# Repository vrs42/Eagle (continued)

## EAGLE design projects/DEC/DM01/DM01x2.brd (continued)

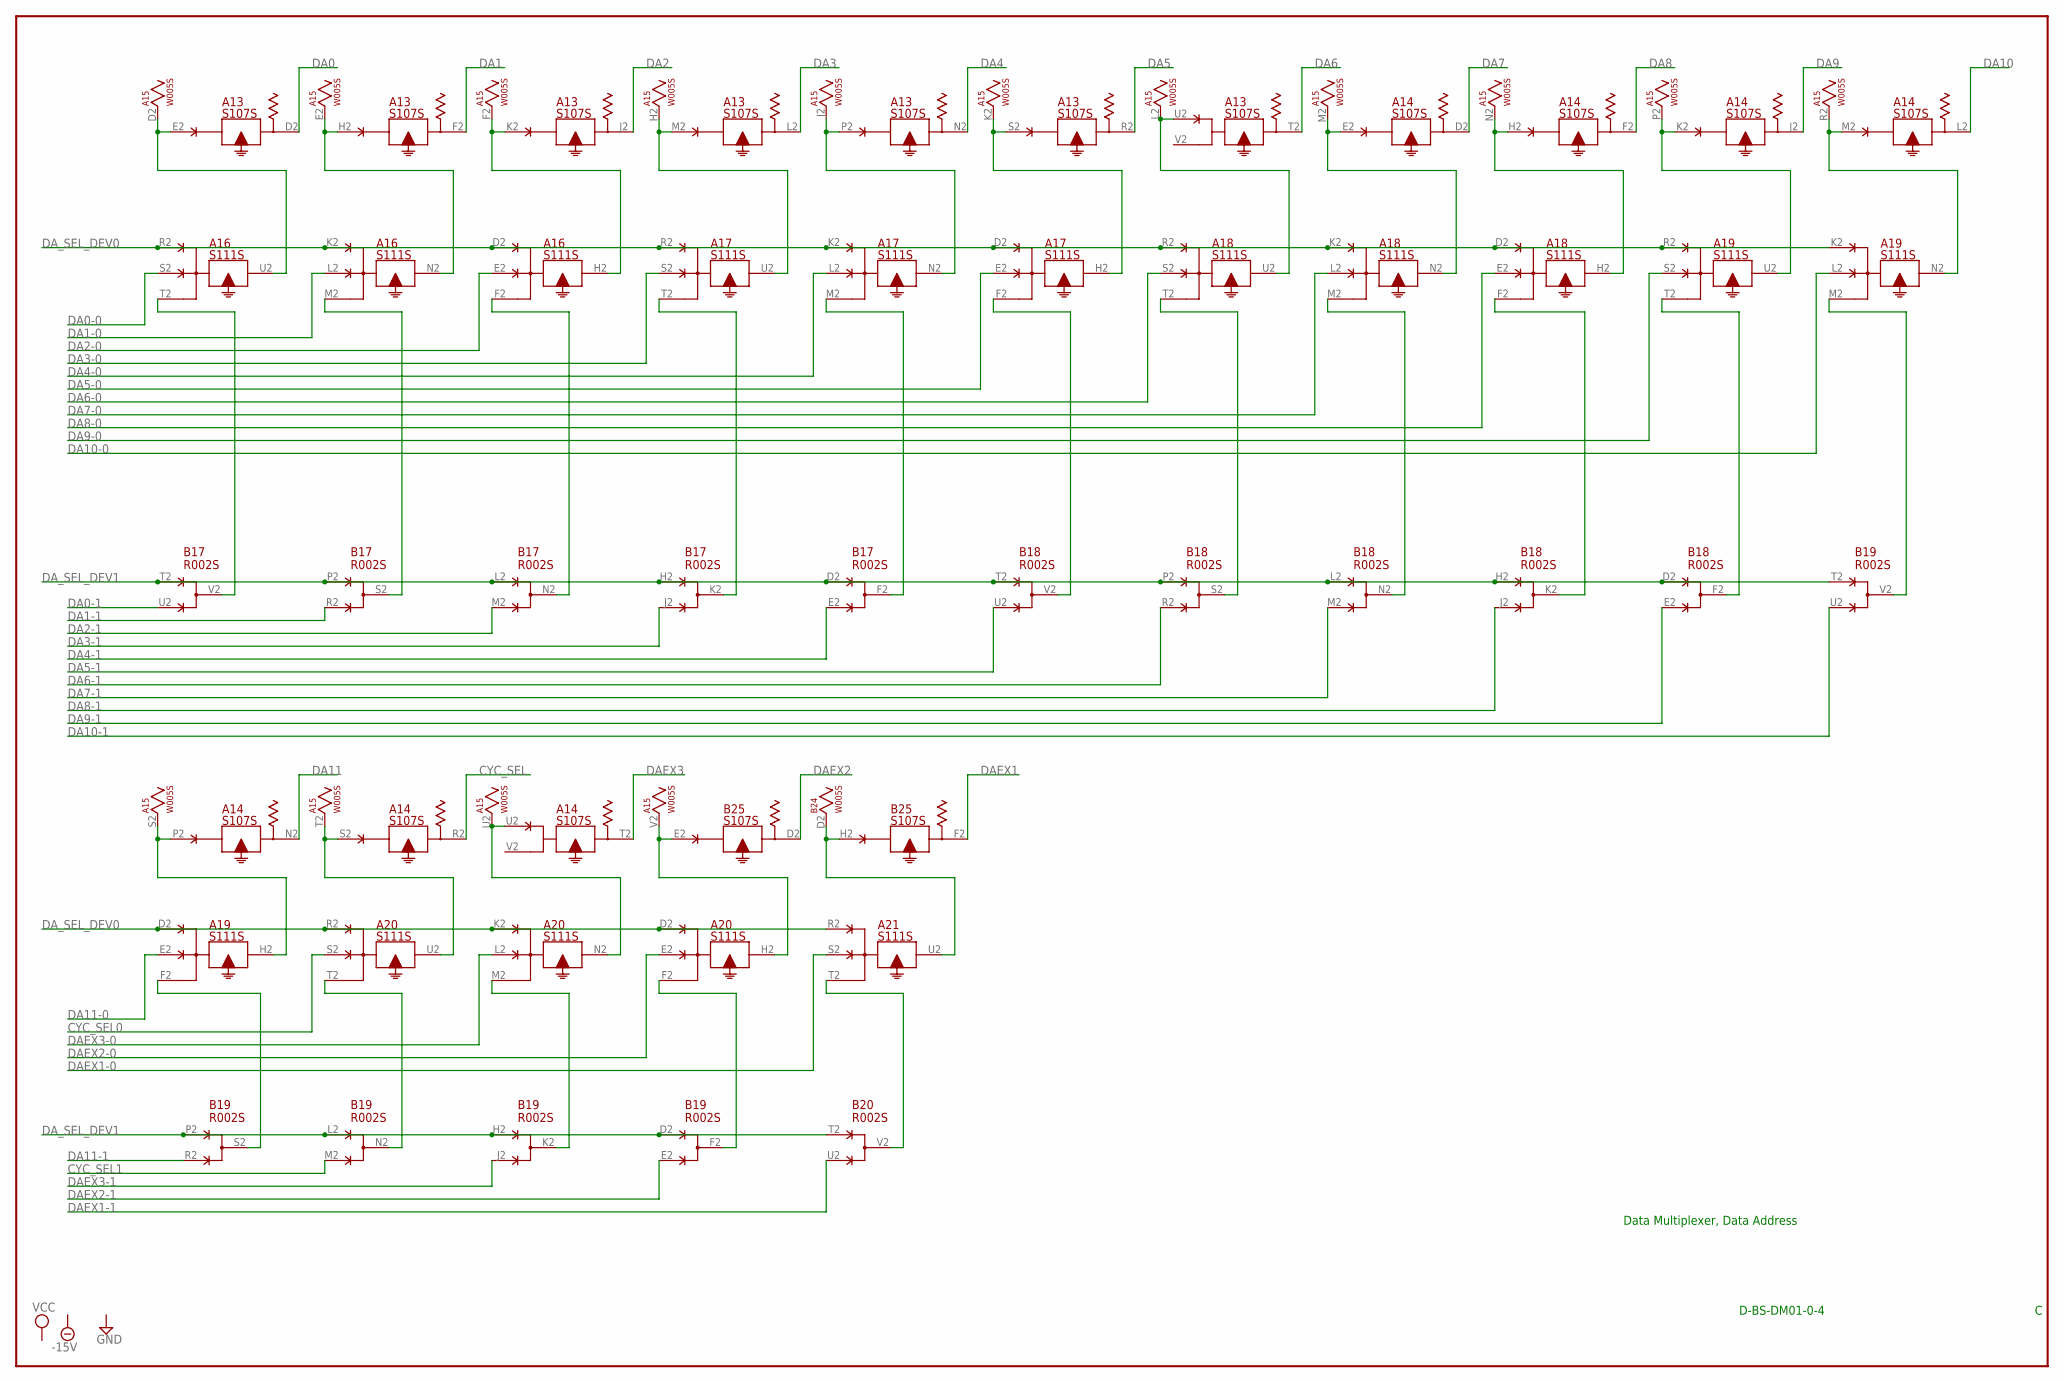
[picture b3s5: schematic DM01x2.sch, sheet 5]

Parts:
A13, A14: S107S; H807S
A15: W005S; H807S
A16, A17, A18, A19, A20, A21: S111S; H807S
B17, B18, B19, B20: R002S; H807S
B24: W005S; H807S
B25: S107S; H807S

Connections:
-15V: A13.B2 (-15V), A14.B2 (-15V), A15.B2 (-15V), A16.B2 (-15V), A17.B2 (-15V), A18.B2 (-15V), A19.B2 (-15V), A20.B2 (-15V), A21.B2 (-15V), B17.B2 (-15V), B18.B2 (-15V), B19.B2 (-15V), B20.B2 (-15V), B24.B2 (-15V), B25.B2 (-15V); also elsewhere on the board
CYC_SEL: A14.R2; also elsewhere on the board
CYC_SEL0: A20.S2; also elsewhere on the board
CYC_SEL1: B19.M2 (E); also elsewhere on the board
DA0: A13.D2; also elsewhere on the board
DA0-0: A16.S2; also elsewhere on the board
DA0-1: B17.U2 (E); also elsewhere on the board
DA1: A13.F2; also elsewhere on the board
DA1-0: A16.L2; also elsewhere on the board
DA1-1: B17.R2 (E); also elsewhere on the board
DA2: A13.J2; also elsewhere on the board
DA2-0: A16.E2; also elsewhere on the board
DA2-1: B17.M2 (E); also elsewhere on the board
DA3: A13.L2; also elsewhere on the board
DA3-0: A17.S2; also elsewhere on the board
DA3-1: B17.J2 (E); also elsewhere on the board
DA4: A13.N2; also elsewhere on the board
DA4-0: A17.L2; also elsewhere on the board
DA4-1: B17.E2 (E); also elsewhere on the board
DA5: A13.R2; also elsewhere on the board
DA5-0: A17.E2; also elsewhere on the board
DA5-1: B18.U2 (E); also elsewhere on the board
DA6: A13.T2; also elsewhere on the board
DA6-0: A18.S2; also elsewhere on the board
DA6-1: B18.R2 (E); also elsewhere on the board
DA7: A14.D2; also elsewhere on the board
DA7-0: A18.L2; also elsewhere on the board
DA7-1: B18.M2 (E); also elsewhere on the board
DA8: A14.F2; also elsewhere on the board
DA8-0: A18.E2; also elsewhere on the board
DA8-1: B18.J2 (E); also elsewhere on the board
DA9: A14.J2; also elsewhere on the board
DA9-0: A19.S2; also elsewhere on the board
DA9-1: B18.E2 (E); also elsewhere on the board
DA10: A14.L2; also elsewhere on the board
DA10-0: A19.L2; also elsewhere on the board
DA10-1: B19.U2 (E); also elsewhere on the board
DA11: A14.N2; also elsewhere on the board
DA11-0: A19.E2; also elsewhere on the board
DA11-1: B19.R2 (E); also elsewhere on the board
DAEX1: B25.F2; also elsewhere on the board
DAEX1-0: A21.S2; also elsewhere on the board
DAEX1-1: B20.U2 (E); also elsewhere on the board
DAEX2: B25.D2; also elsewhere on the board
DAEX2-0: A20.E2; also elsewhere on the board
DAEX2-1: B19.E2 (E); also elsewhere on the board
DAEX3: A14.T2; also elsewhere on the board
DAEX3-0: A20.L2; also elsewhere on the board
DAEX3-1: B19.J2 (E); also elsewhere on the board
DA_SEL_DEV0: A16.D2, A16.K2, A16.R2, A17.D2, A17.K2, A17.R2, A18.D2, A18.K2, A18.R2, A19.D2, A19.K2, A19.R2, A20.D2, A20.K2, A20.R2, A21.R2; also elsewhere on the board
DA_SEL_DEV1: B17.D2 (D), B17.H2 (D), B17.L2 (D), B17.P2 (D), B17.T2 (D), B18.D2 (D), B18.H2 (D), B18.L2 (D), B18.P2 (D), B18.T2 (D), B19.D2 (D), B19.H2 (D), B19.L2 (D), B19.P2 (D), B19.T2 (D), B20.T2 (D); also elsewhere on the board
GND: A13.C2 (GND), A14.C2 (GND), A15.C2 (GND), A16.C2 (GND), A17.C2 (GND), A18.C2 (GND), A19.C2 (GND), A20.C2 (GND), A21.C2 (GND), B17.C2 (GND), B18.C2 (GND), B19.C2 (GND), B20.C2 (GND), B24.C2 (GND), B25.C2 (GND); also elsewhere on the board
unnamed: A19.F2, B19.S2 (F)
unnamed: A20.T2, B19.N2 (F)
unnamed: A20.M2, B19.K2 (F)
unnamed: A20.F2, B19.F2 (F)
unnamed: A21.T2, B20.V2 (F)
unnamed: A16.T2, B17.V2 (F)
unnamed: A19.M2, B19.V2 (F)
unnamed: A19.T2, B18.F2 (F)
unnamed: A18.F2, B18.K2 (F)
unnamed: A18.M2, B18.N2 (F)
unnamed: A18.T2, B18.S2 (F)
unnamed: A17.F2, B18.V2 (F)
unnamed: A17.M2, B17.F2 (F)
unnamed: A17.T2, B17.K2 (F)
unnamed: A16.F2, B17.N2 (F)
unnamed: A16.M2, B17.S2 (F)
unnamed: A13.E2, A15.D2, A16.U2
unnamed: A13.U2, A15.L2, A18.U2
unnamed: A13.H2, A15.E2, A16.N2
unnamed: A13.K2, A15.F2, A16.H2
unnamed: A13.M2, A15.H2, A17.U2
unnamed: A13.P2, A15.J2, A17.N2
unnamed: A13.S2, A15.K2, A17.H2
unnamed: A14.E2, A15.M2, A18.N2
unnamed: A14.H2, A15.N2, A18.H2
unnamed: A14.K2, A15.P2, A19.U2
unnamed: A14.M2, A15.R2, A19.N2
unnamed: A14.P2, A15.S2, A19.H2
unnamed: A14.S2, A15.T2, A20.U2
unnamed: A14.U2, A15.U2, A20.N2
unnamed: A15.V2, A20.H2, B25.E2
unnamed: A21.U2, B24.D2, B25.H2
VCC: A13.A2 (VCC), A14.A2 (VCC), A15.A2 (VCC), A16.A2 (VCC), A17.A2 (VCC), A18.A2 (VCC), A19.A2 (VCC), A20.A2 (VCC), A21.A2 (VCC), B17.A2 (VCC), B18.A2 (VCC), B19.A2 (VCC), B20.A2 (VCC), B24.A2 (VCC), B25.A2 (VCC); also elsewhere on the board

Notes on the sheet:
D-BS-DM01-0-4
Data Multiplexer, Data Address

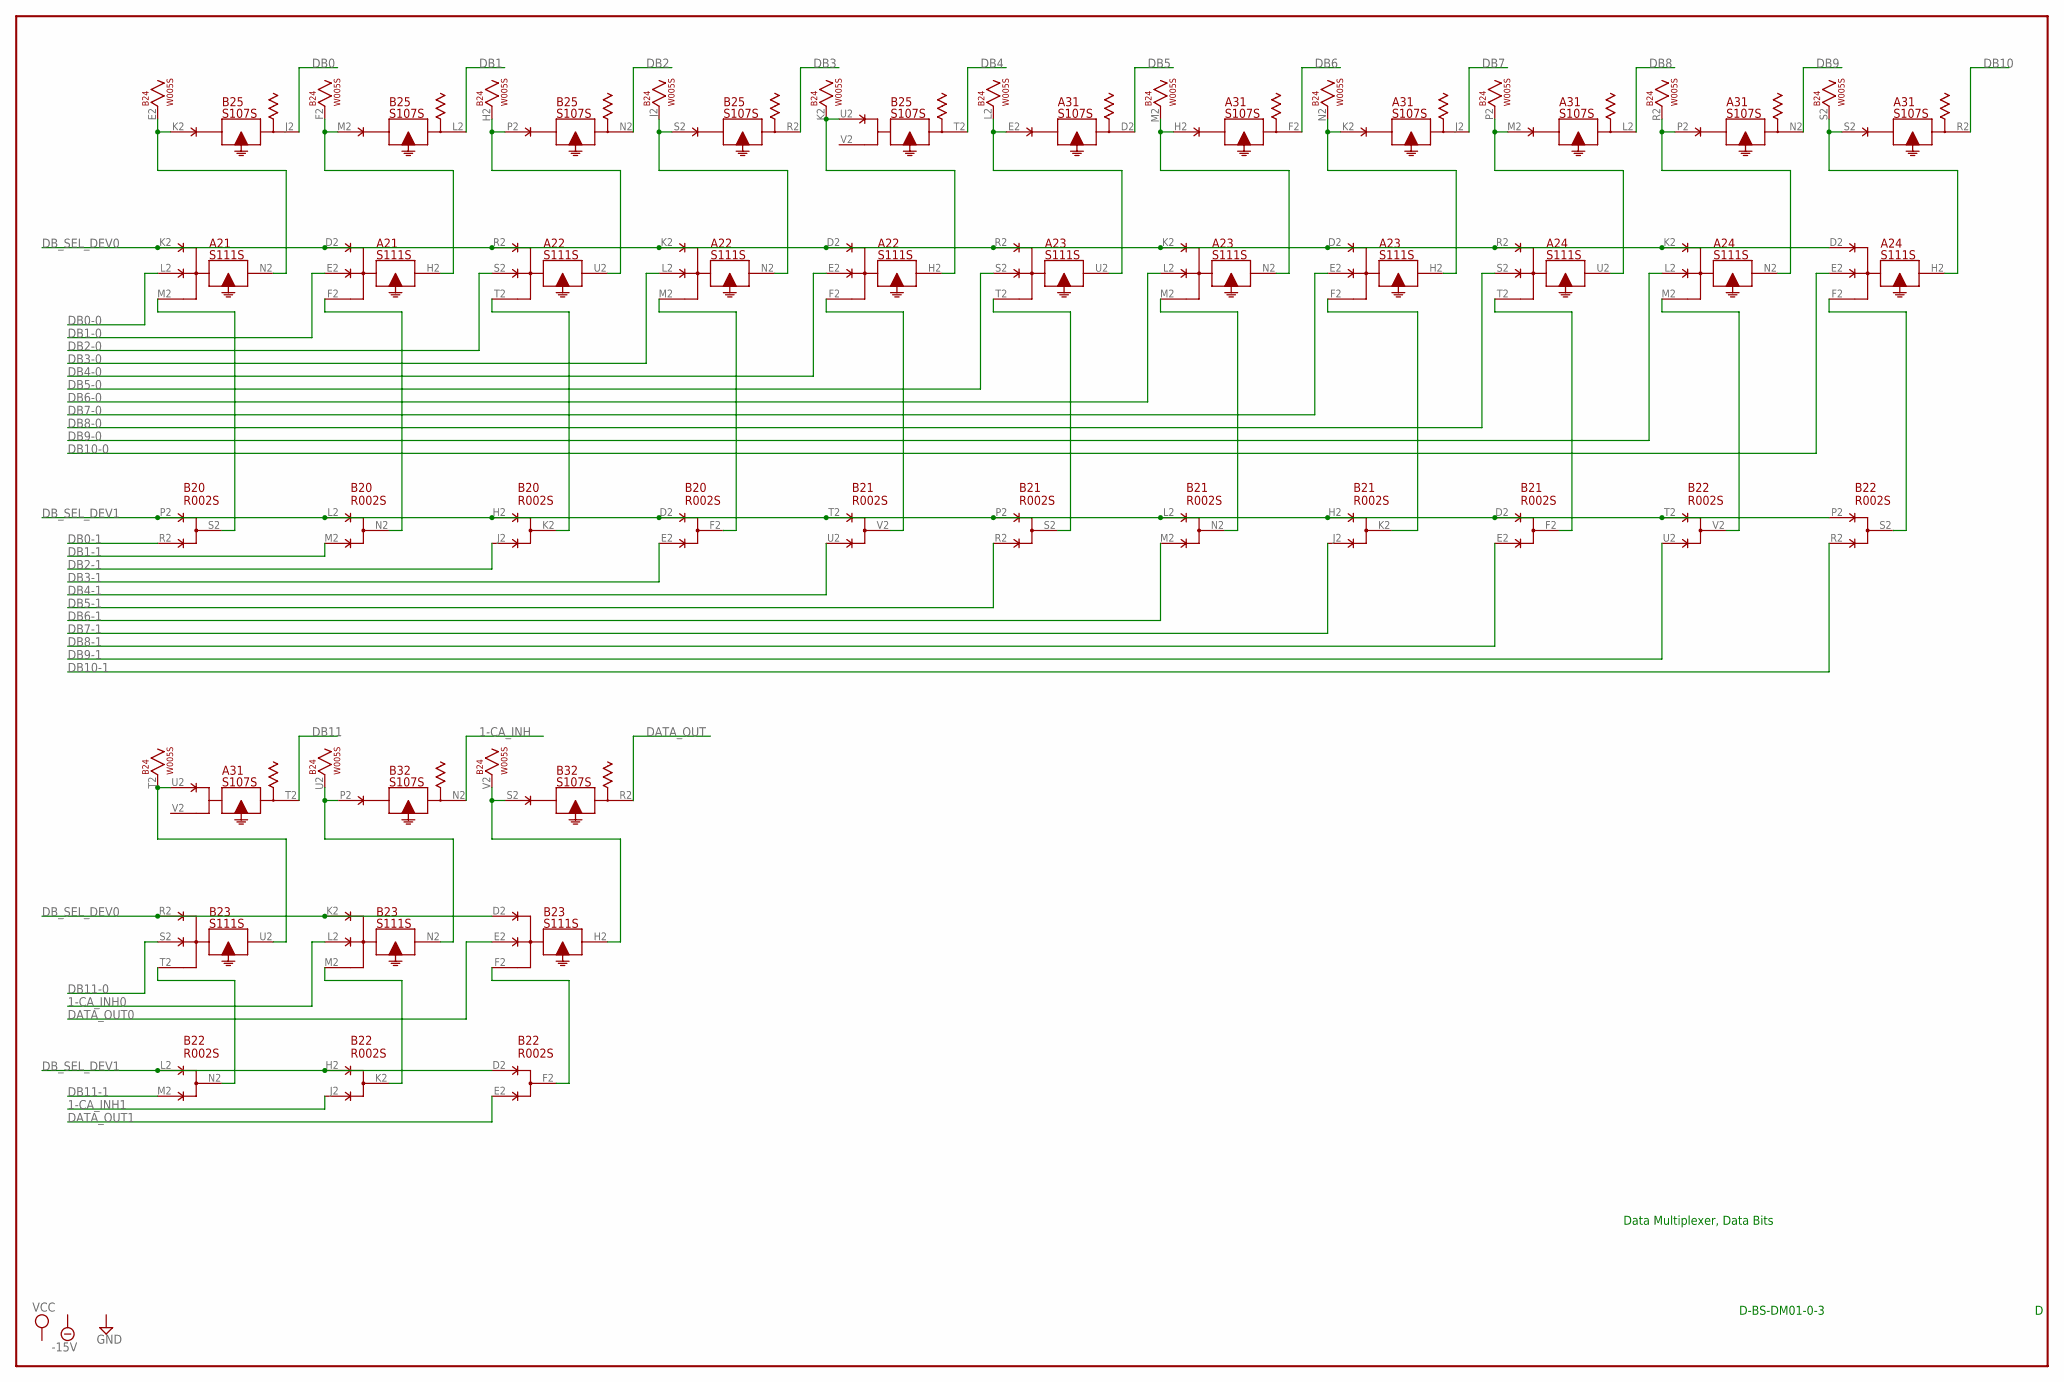
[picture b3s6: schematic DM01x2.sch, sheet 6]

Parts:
A21, A22, A23, A24: S111S; H807S
A31: S107S; H807S
B20, B21, B22: R002S; H807S
B23: S111S; H807S
B24: W005S; H807S
B25, B32: S107S; H807S

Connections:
1-CA_INH: B32.N2; also elsewhere on the board
1-CA_INH0: B23.L2; also elsewhere on the board
1-CA_INH1: B22.J2 (E); also elsewhere on the board
-15V: A21.B2 (-15V), A22.B2 (-15V), A23.B2 (-15V), A24.B2 (-15V), A31.B2 (-15V), B20.B2 (-15V), B21.B2 (-15V), B22.B2 (-15V), B23.B2 (-15V), B24.B2 (-15V), B25.B2 (-15V), B32.B2 (-15V); also elsewhere on the board
DATA_OUT: B32.R2; also elsewhere on the board
DATA_OUT0: B23.E2; also elsewhere on the board
DATA_OUT1: B22.E2 (E); also elsewhere on the board
DB0: B25.J2; also elsewhere on the board
DB0-0: A21.L2; also elsewhere on the board
DB0-1: B20.R2 (E); also elsewhere on the board
DB1: B25.L2; also elsewhere on the board
DB1-0: A21.E2; also elsewhere on the board
DB1-1: B20.M2 (E); also elsewhere on the board
DB2: B25.N2; also elsewhere on the board
DB2-0: A22.S2; also elsewhere on the board
DB2-1: B20.J2 (E); also elsewhere on the board
DB3: B25.R2; also elsewhere on the board
DB3-0: A22.L2; also elsewhere on the board
DB3-1: B20.E2 (E); also elsewhere on the board
DB4: B25.T2; also elsewhere on the board
DB4-0: A22.E2; also elsewhere on the board
DB4-1: B21.U2 (E); also elsewhere on the board
DB5: A31.D2; also elsewhere on the board
DB5-0: A23.S2; also elsewhere on the board
DB5-1: B21.R2 (E); also elsewhere on the board
DB6: A31.F2; also elsewhere on the board
DB6-0: A23.L2; also elsewhere on the board
DB6-1: B21.M2 (E); also elsewhere on the board
DB7: A31.J2; also elsewhere on the board
DB7-0: A23.E2; also elsewhere on the board
DB7-1: B21.J2 (E); also elsewhere on the board
DB8: A31.L2; also elsewhere on the board
DB8-0: A24.S2; also elsewhere on the board
DB8-1: B21.E2 (E); also elsewhere on the board
DB9: A31.N2; also elsewhere on the board
DB9-0: A24.L2; also elsewhere on the board
DB9-1: B22.U2 (E); also elsewhere on the board
DB10: A31.R2; also elsewhere on the board
DB10-0: A24.E2; also elsewhere on the board
DB10-1: B22.R2 (E); also elsewhere on the board
DB11: A31.T2; also elsewhere on the board
DB11-0: B23.S2; also elsewhere on the board
DB11-1: B22.M2 (E); also elsewhere on the board
DB_SEL_DEV0: A21.D2, A21.K2, A22.D2, A22.K2, A22.R2, A23.D2, A23.K2, A23.R2, A24.D2, A24.K2, A24.R2, B23.D2, B23.K2, B23.R2; also elsewhere on the board
DB_SEL_DEV1: B20.D2 (D), B20.H2 (D), B20.L2 (D), B20.P2 (D), B21.D2 (D), B21.H2 (D), B21.L2 (D), B21.P2 (D), B21.T2 (D), B22.D2 (D), B22.H2 (D), B22.L2 (D), B22.P2 (D), B22.T2 (D); also elsewhere on the board
GND: A21.C2 (GND), A22.C2 (GND), A23.C2 (GND), A24.C2 (GND), A31.C2 (GND), B20.C2 (GND), B21.C2 (GND), B22.C2 (GND), B23.C2 (GND), B24.C2 (GND), B25.C2 (GND), B32.C2 (GND); also elsewhere on the board
unnamed: B22.F2 (F), B23.F2
unnamed: B22.N2 (F), B23.T2
unnamed: B22.K2 (F), B23.M2
unnamed: A24.F2, B22.S2 (F)
unnamed: A21.M2, B20.S2 (F)
unnamed: A21.F2, B20.N2 (F)
unnamed: A22.T2, B20.K2 (F)
unnamed: A22.M2, B20.F2 (F)
unnamed: A22.F2, B21.V2 (F)
unnamed: A23.T2, B21.S2 (F)
unnamed: A23.M2, B21.N2 (F)
unnamed: A23.F2, B21.K2 (F)
unnamed: A24.T2, B21.F2 (F)
unnamed: A24.M2, B22.V2 (F)
unnamed: A21.N2, B24.E2, B25.K2
unnamed: A21.H2, B24.F2, B25.M2
unnamed: A22.U2, B24.H2, B25.P2
unnamed: A22.N2, B24.J2, B25.S2
unnamed: A22.H2, B24.K2, B25.U2
unnamed: A23.U2, A31.E2, B24.L2
unnamed: A23.N2, A31.H2, B24.M2
unnamed: A23.H2, A31.K2, B24.N2
unnamed: A24.U2, A31.M2, B24.P2
unnamed: A24.N2, A31.P2, B24.R2
unnamed: A24.H2, A31.S2, B24.S2
unnamed: A31.U2, B23.U2, B24.T2
unnamed: B23.N2, B24.U2, B32.P2
unnamed: B23.H2, B24.V2, B32.S2
VCC: A21.A2 (VCC), A22.A2 (VCC), A23.A2 (VCC), A24.A2 (VCC), A31.A2 (VCC), B20.A2 (VCC), B21.A2 (VCC), B22.A2 (VCC), B23.A2 (VCC), B24.A2 (VCC), B25.A2 (VCC), B32.A2 (VCC); also elsewhere on the board

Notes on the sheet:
D-BS-DM01-0-3
Data Multiplexer, Data Bits

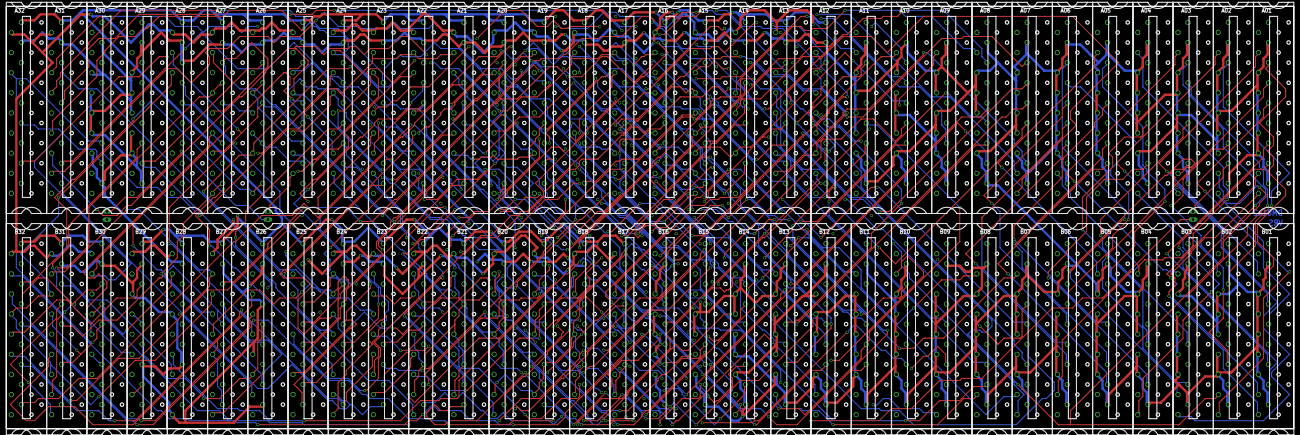
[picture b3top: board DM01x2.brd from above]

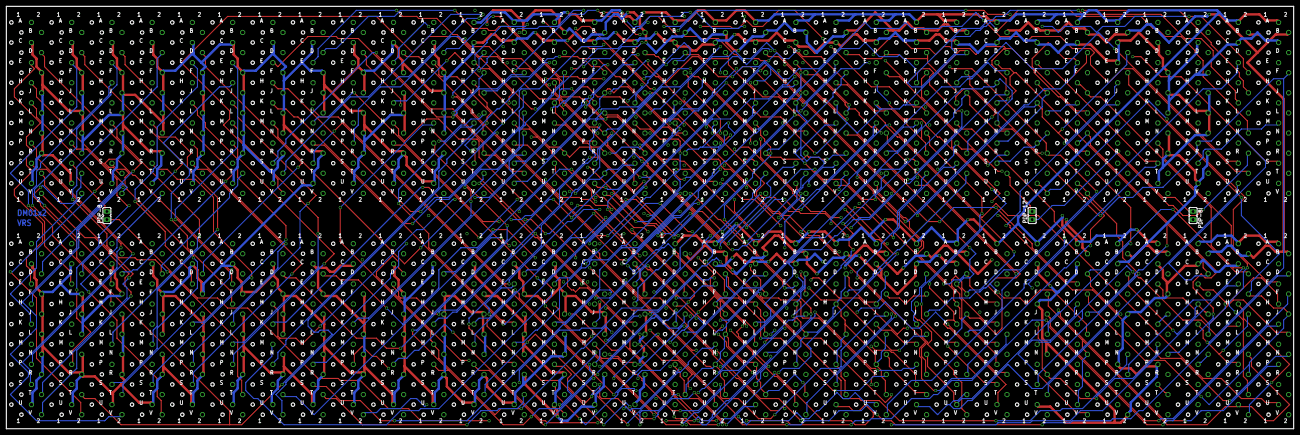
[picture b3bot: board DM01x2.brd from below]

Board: 4 copper layers, 406.4 x 133.3 mm, 75 parts (3 on the bottom side), 256 nets.

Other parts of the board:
U$9, U$10, U$11, U$12, U$13, U$14, U$15, U$16: CBLOCK

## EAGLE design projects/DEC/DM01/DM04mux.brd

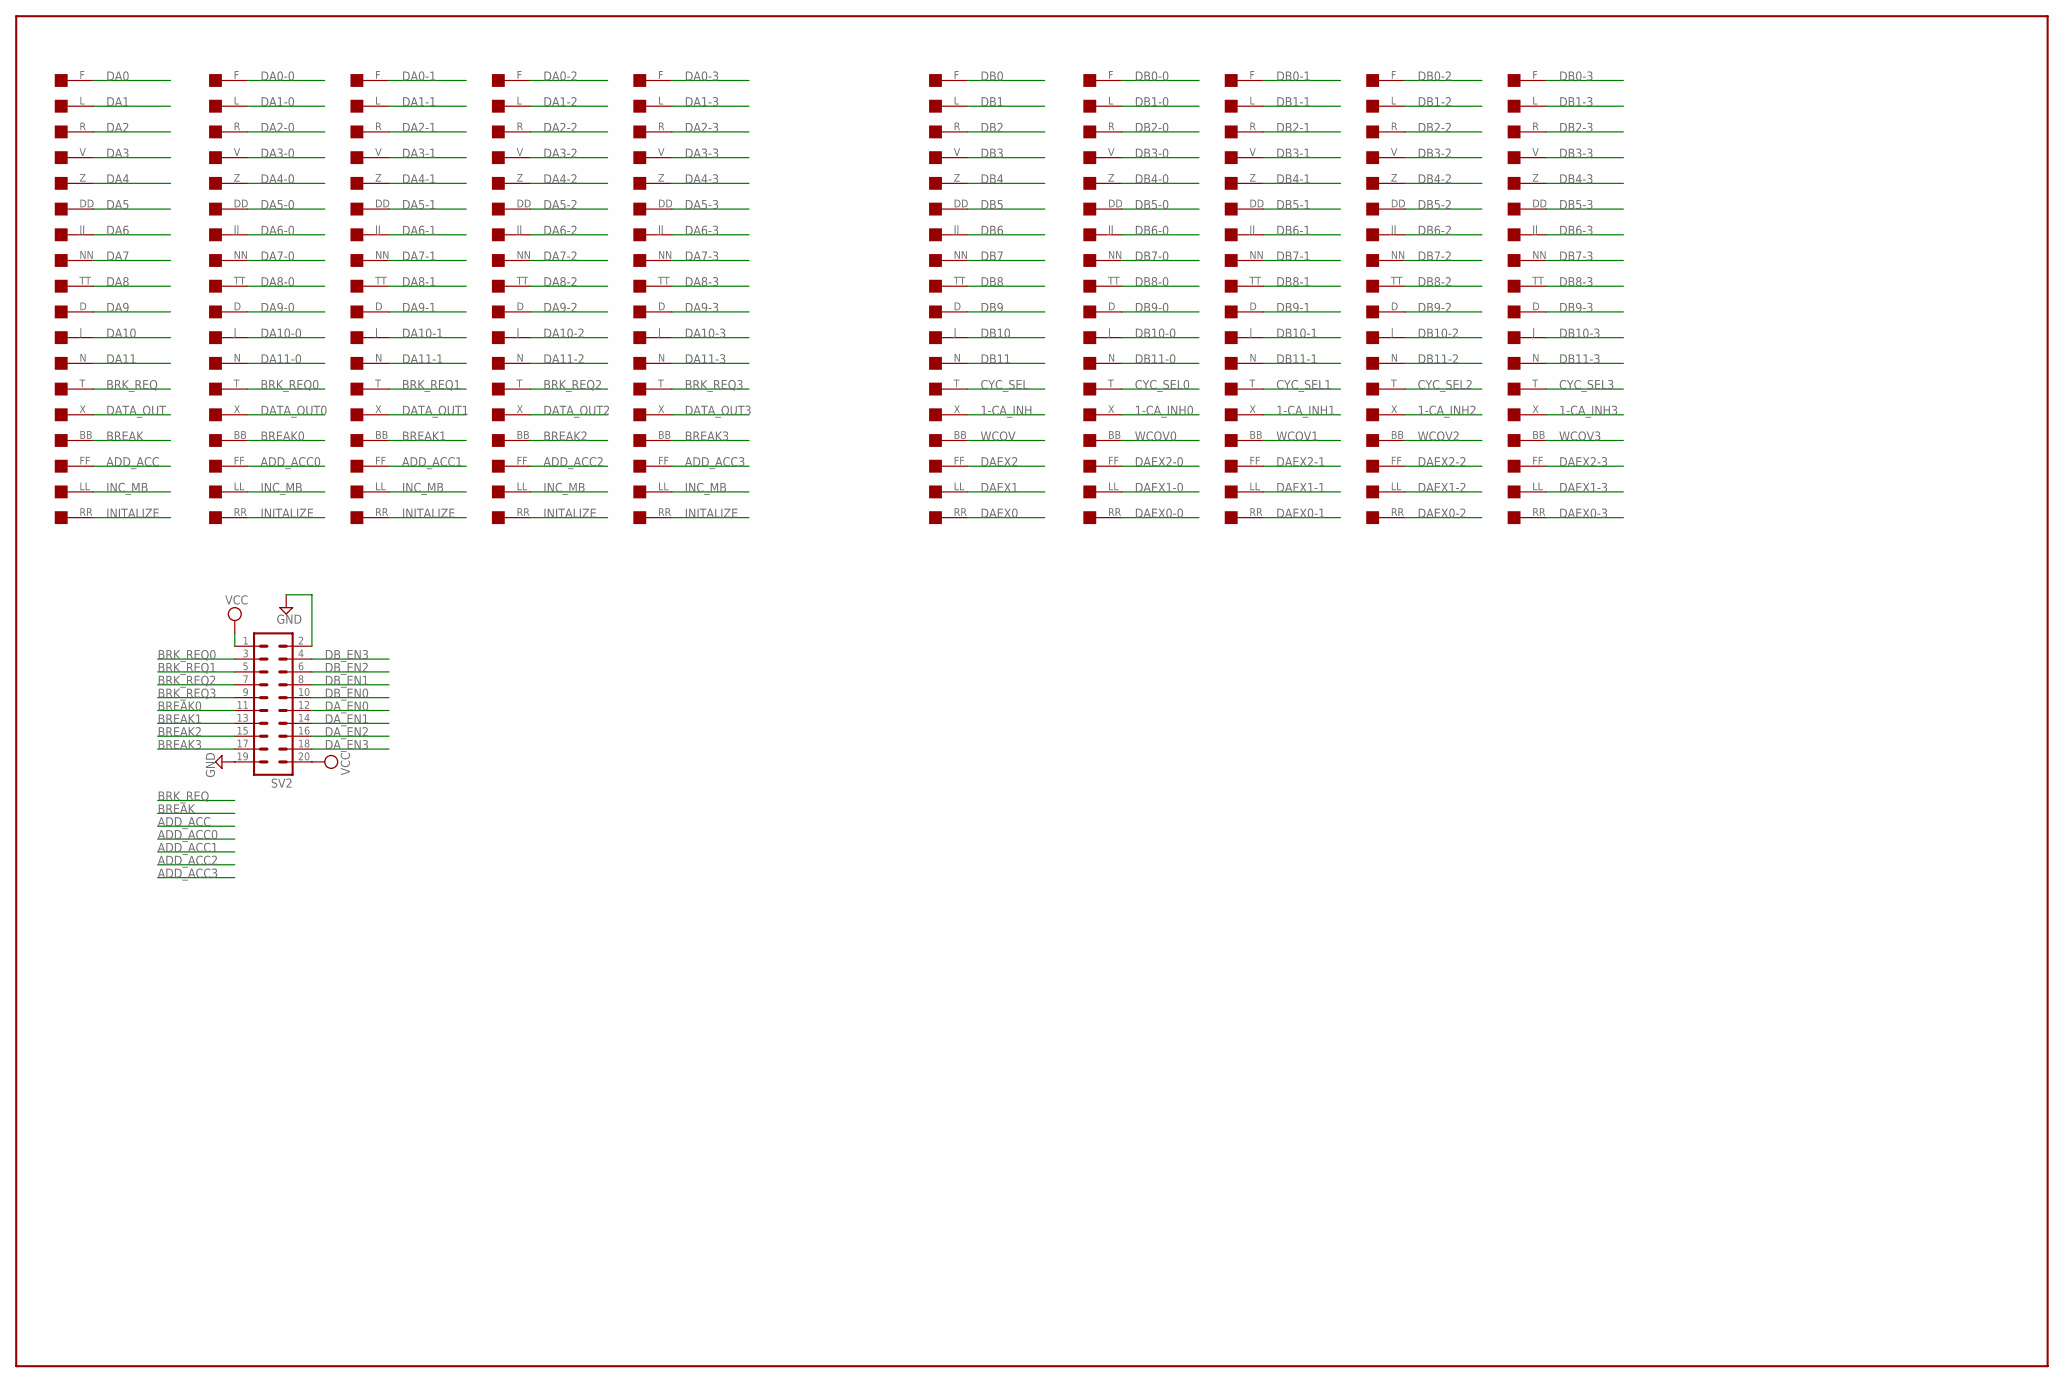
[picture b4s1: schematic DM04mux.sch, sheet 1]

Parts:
SV2: MA10-2
U$1, U$2, U$3, U$4, U$5, U$6, U$7, U$8, U$9, U$10: BC08J; DEC40PINV

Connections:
1-CA_INH: U$6.X (1); also elsewhere on the board
1-CA_INH0: U$7.X (1); also elsewhere on the board
1-CA_INH1: U$8.X (1); also elsewhere on the board
1-CA_INH2: U$9.X (1); also elsewhere on the board
1-CA_INH3: U$10.X (1); also elsewhere on the board
ADD_ACC: U$1.FF (1)
ADD_ACC0: U$2.FF (1)
ADD_ACC1: U$3.FF (1)
ADD_ACC2: U$4.FF (1)
ADD_ACC3: U$5.FF (1)
BREAK: U$1.BB (1)
BREAK0: SV2.11, U$2.BB (1)
BREAK1: SV2.13, U$3.BB (1)
BREAK2: SV2.15, U$4.BB (1)
BREAK3: SV2.17, U$5.BB (1)
BRK_REQ: U$1.T (1)
BRK_REQ0: SV2.3, U$2.T (1)
BRK_REQ1: SV2.5, U$3.T (1)
BRK_REQ2: SV2.7, U$4.T (1)
BRK_REQ3: SV2.9, U$5.T (1)
CYC_SEL: U$6.T (1); also elsewhere on the board
CYC_SEL0: U$7.T (1); also elsewhere on the board
CYC_SEL1: U$8.T (1); also elsewhere on the board
CYC_SEL2: U$9.T (1); also elsewhere on the board
CYC_SEL3: U$10.T (1); also elsewhere on the board
DA0: U$1.F (1); also elsewhere on the board
DA0-0: U$2.F (1); also elsewhere on the board
DA0-1: U$3.F (1); also elsewhere on the board
DA0-2: U$4.F (1); also elsewhere on the board
DA0-3: U$5.F (1); also elsewhere on the board
DA1: U$1.L (1); also elsewhere on the board
DA1-0: U$2.L (1); also elsewhere on the board
DA1-1: U$3.L (1); also elsewhere on the board
DA1-2: U$4.L (1); also elsewhere on the board
DA1-3: U$5.L (1); also elsewhere on the board
DA2: U$1.R (1); also elsewhere on the board
DA2-0: U$2.R (1); also elsewhere on the board
DA2-1: U$3.R (1); also elsewhere on the board
DA2-2: U$4.R (1); also elsewhere on the board
DA2-3: U$5.R (1); also elsewhere on the board
DA3: U$1.V (1); also elsewhere on the board
DA3-0: U$2.V (1); also elsewhere on the board
DA3-1: U$3.V (1); also elsewhere on the board
DA3-2: U$4.V (1); also elsewhere on the board
DA3-3: U$5.V (1); also elsewhere on the board
DA4: U$1.Z (1); also elsewhere on the board
DA4-0: U$2.Z (1); also elsewhere on the board
DA4-1: U$3.Z (1); also elsewhere on the board
DA4-2: U$4.Z (1); also elsewhere on the board
DA4-3: U$5.Z (1); also elsewhere on the board
DA5: U$1.DD (1); also elsewhere on the board
DA5-0: U$2.DD (1); also elsewhere on the board
DA5-1: U$3.DD (1); also elsewhere on the board
DA5-2: U$4.DD (1); also elsewhere on the board
DA5-3: U$5.DD (1); also elsewhere on the board
DA6: U$1.JJ (1); also elsewhere on the board
DA6-0: U$2.JJ (1); also elsewhere on the board
DA6-1: U$3.JJ (1); also elsewhere on the board
DA6-2: U$4.JJ (1); also elsewhere on the board
DA6-3: U$5.JJ (1); also elsewhere on the board
DA7: U$1.NN (1); also elsewhere on the board
DA7-0: U$2.NN (1); also elsewhere on the board
DA7-1: U$3.NN (1); also elsewhere on the board
DA7-2: U$4.NN (1); also elsewhere on the board
DA7-3: U$5.NN (1); also elsewhere on the board
DA8: U$1.TT (1); also elsewhere on the board
DA8-0: U$2.TT (1); also elsewhere on the board
DA8-1: U$3.TT (1); also elsewhere on the board
DA8-2: U$4.TT (1); also elsewhere on the board
DA8-3: U$5.TT (1); also elsewhere on the board
DA9: U$1.D (1); also elsewhere on the board
DA9-0: U$2.D (1); also elsewhere on the board
DA9-1: U$3.D (1); also elsewhere on the board
DA9-2: U$4.D (1); also elsewhere on the board
DA9-3: U$5.D (1); also elsewhere on the board
DA10: U$1.J (1); also elsewhere on the board
DA10-0: U$2.J (1); also elsewhere on the board
DA10-1: U$3.J (1); also elsewhere on the board
DA10-2: U$4.J (1); also elsewhere on the board
DA10-3: U$5.J (1); also elsewhere on the board
DA11: U$1.N (1); also elsewhere on the board
DA11-0: U$2.N (1); also elsewhere on the board
DA11-1: U$3.N (1); also elsewhere on the board
DA11-2: U$4.N (1); also elsewhere on the board
DA11-3: U$5.N (1); also elsewhere on the board
DAEX0: U$6.RR (1); also elsewhere on the board
DAEX0-0: U$7.RR (1); also elsewhere on the board
DAEX0-1: U$8.RR (1); also elsewhere on the board
DAEX0-2: U$9.RR (1); also elsewhere on the board
DAEX0-3: U$10.RR (1); also elsewhere on the board
DAEX1: U$6.LL (1); also elsewhere on the board
DAEX1-0: U$7.LL (1); also elsewhere on the board
DAEX1-1: U$8.LL (1); also elsewhere on the board
DAEX1-2: U$9.LL (1); also elsewhere on the board
DAEX1-3: U$10.LL (1); also elsewhere on the board
DAEX2: U$6.FF (1); also elsewhere on the board
DAEX2-0: U$7.FF (1); also elsewhere on the board
DAEX2-1: U$8.FF (1); also elsewhere on the board
DAEX2-2: U$9.FF (1); also elsewhere on the board
DAEX2-3: U$10.FF (1); also elsewhere on the board
DATA_OUT: U$1.X (1); also elsewhere on the board
DATA_OUT0: U$2.X (1); also elsewhere on the board
DATA_OUT1: U$3.X (1); also elsewhere on the board
DATA_OUT2: U$4.X (1); also elsewhere on the board
DATA_OUT3: U$5.X (1); also elsewhere on the board
DA_EN0: SV2.12; also elsewhere on the board
DA_EN1: SV2.14; also elsewhere on the board
DA_EN2: SV2.16; also elsewhere on the board
DA_EN3: SV2.18; also elsewhere on the board
DB0: U$6.F (1); also elsewhere on the board
DB0-0: U$7.F (1); also elsewhere on the board
DB0-1: U$8.F (1); also elsewhere on the board
DB0-2: U$9.F (1); also elsewhere on the board
DB0-3: U$10.F (1); also elsewhere on the board
DB1: U$6.L (1); also elsewhere on the board
DB1-0: U$7.L (1); also elsewhere on the board
DB1-1: U$8.L (1); also elsewhere on the board
DB1-2: U$9.L (1); also elsewhere on the board
DB1-3: U$10.L (1); also elsewhere on the board
DB2: U$6.R (1); also elsewhere on the board
DB2-0: U$7.R (1); also elsewhere on the board
DB2-1: U$8.R (1); also elsewhere on the board
DB2-2: U$9.R (1); also elsewhere on the board
DB2-3: U$10.R (1); also elsewhere on the board
DB3: U$6.V (1); also elsewhere on the board
DB3-0: U$7.V (1); also elsewhere on the board
DB3-1: U$8.V (1); also elsewhere on the board
DB3-2: U$9.V (1); also elsewhere on the board
DB3-3: U$10.V (1); also elsewhere on the board
DB4: U$6.Z (1); also elsewhere on the board
DB4-0: U$7.Z (1); also elsewhere on the board
DB4-1: U$8.Z (1); also elsewhere on the board
DB4-2: U$9.Z (1); also elsewhere on the board
DB4-3: U$10.Z (1); also elsewhere on the board
DB5: U$6.DD (1); also elsewhere on the board
DB5-0: U$7.DD (1); also elsewhere on the board
DB5-1: U$8.DD (1); also elsewhere on the board
DB5-2: U$9.DD (1); also elsewhere on the board
DB5-3: U$10.DD (1); also elsewhere on the board
DB6: U$6.JJ (1); also elsewhere on the board
DB6-0: U$7.JJ (1); also elsewhere on the board
DB6-1: U$8.JJ (1); also elsewhere on the board
DB6-2: U$9.JJ (1); also elsewhere on the board
DB6-3: U$10.JJ (1); also elsewhere on the board
DB7: U$6.NN (1); also elsewhere on the board
DB7-0: U$7.NN (1); also elsewhere on the board
DB7-1: U$8.NN (1); also elsewhere on the board
DB7-2: U$9.NN (1); also elsewhere on the board
DB7-3: U$10.NN (1); also elsewhere on the board
DB8: U$6.TT (1); also elsewhere on the board
DB8-0: U$7.TT (1); also elsewhere on the board
DB8-1: U$8.TT (1); also elsewhere on the board
DB8-2: U$9.TT (1); also elsewhere on the board
DB8-3: U$10.TT (1); also elsewhere on the board
DB9: U$6.D (1); also elsewhere on the board
DB9-0: U$7.D (1); also elsewhere on the board
DB9-1: U$8.D (1); also elsewhere on the board
DB9-2: U$9.D (1); also elsewhere on the board
DB9-3: U$10.D (1); also elsewhere on the board
DB10: U$6.J (1); also elsewhere on the board
DB10-0: U$7.J (1); also elsewhere on the board
DB10-1: U$8.J (1); also elsewhere on the board
DB10-2: U$9.J (1); also elsewhere on the board
DB10-3: U$10.J (1); also elsewhere on the board
DB11: U$6.N (1); also elsewhere on the board
DB11-0: U$7.N (1); also elsewhere on the board
DB11-1: U$8.N (1); also elsewhere on the board
DB11-2: U$9.N (1); also elsewhere on the board
DB11-3: U$10.N (1); also elsewhere on the board
DB_EN0: SV2.10; also elsewhere on the board
DB_EN1: SV2.8; also elsewhere on the board
DB_EN2: SV2.6; also elsewhere on the board
DB_EN3: SV2.4; also elsewhere on the board
GND: SV2.2, SV2.19, U$1.A (GND), U$1.AA (GND), U$1.B (GND), U$1.C (GND), U$1.CC (GND), U$1.E (GND), U$1.EE (GND), U$1.H (GND), U$1.HH (GND), U$1.K (GND), U$1.KK (GND), U$1.M (GND), U$1.MM (GND), U$1.P (GND), U$1.PP (GND), U$1.S (GND), U$1.SS (GND), U$1.U (GND), U$1.UU (GND), U$1.VV (GND), U$1.W (GND), U$1.Y (GND), U$2.A (GND), U$2.AA (GND), U$2.B (GND), U$2.C (GND), U$2.CC (GND), U$2.E (GND), U$2.EE (GND), U$2.H (GND), U$2.HH (GND), U$2.K (GND), U$2.KK (GND), U$2.M (GND), U$2.MM (GND), U$2.P (GND), U$2.PP (GND), U$2.S (GND), U$2.SS (GND), U$2.U (GND), U$2.UU (GND), U$2.VV (GND), U$2.W (GND), U$2.Y (GND), U$3.A (GND), U$3.AA (GND), U$3.B (GND), U$3.C (GND), U$3.CC (GND), U$3.E (GND), U$3.EE (GND), U$3.H (GND), U$3.HH (GND), U$3.K (GND), U$3.KK (GND), U$3.M (GND), U$3.MM (GND), U$3.P (GND), U$3.PP (GND), U$3.S (GND), U$3.SS (GND), U$3.U (GND), U$3.UU (GND), U$3.VV (GND), U$3.W (GND), U$3.Y (GND), U$4.A (GND), U$4.AA (GND), U$4.B (GND), U$4.C (GND), U$4.CC (GND), U$4.E (GND), U$4.EE (GND), U$4.H (GND), U$4.HH (GND), U$4.K (GND), U$4.KK (GND), U$4.M (GND), U$4.MM (GND), U$4.P (GND), U$4.PP (GND), U$4.S (GND), U$4.SS (GND), U$4.U (GND), U$4.UU (GND), U$4.VV (GND), U$4.W (GND), U$4.Y (GND), U$5.A (GND), U$5.AA (GND), U$5.B (GND), U$5.C (GND), U$5.CC (GND), U$5.E (GND), U$5.EE (GND), U$5.H (GND), U$5.HH (GND), U$5.K (GND), U$5.KK (GND), U$5.M (GND), U$5.MM (GND), U$5.P (GND), U$5.PP (GND), U$5.S (GND), U$5.SS (GND), U$5.U (GND), U$5.UU (GND), U$5.VV (GND), U$5.W (GND), U$5.Y (GND), U$6.A (GND), U$6.AA (GND), U$6.B (GND), U$6.C (GND), U$6.CC (GND), U$6.E (GND), U$6.EE (GND), U$6.H (GND), U$6.HH (GND), U$6.K (GND), U$6.KK (GND), U$6.M (GND), U$6.MM (GND), U$6.P (GND), U$6.PP (GND), U$6.S (GND), U$6.SS (GND), U$6.U (GND), U$6.UU (GND), U$6.VV (GND), U$6.W (GND), U$6.Y (GND), U$7.A (GND), U$7.AA (GND), U$7.B (GND), U$7.C (GND), U$7.CC (GND), U$7.E (GND), U$7.EE (GND), U$7.H (GND), U$7.HH (GND), U$7.K (GND), U$7.KK (GND), U$7.M (GND), U$7.MM (GND), U$7.P (GND), U$7.PP (GND), U$7.S (GND), U$7.SS (GND), U$7.U (GND), U$7.UU (GND), U$7.VV (GND), U$7.W (GND), U$7.Y (GND), U$8.A (GND), U$8.AA (GND), U$8.B (GND), U$8.C (GND), U$8.CC (GND), U$8.E (GND), U$8.EE (GND), U$8.H (GND), U$8.HH (GND), U$8.K (GND), U$8.KK (GND), U$8.M (GND), U$8.MM (GND), U$8.P (GND), U$8.PP (GND), U$8.S (GND), U$8.SS (GND), U$8.U (GND), U$8.UU (GND), U$8.VV (GND), U$8.W (GND), U$8.Y (GND), U$9.A (GND), U$9.AA (GND), U$9.B (GND), U$9.C (GND), U$9.CC (GND), U$9.E (GND), U$9.EE (GND), U$9.H (GND), U$9.HH (GND), U$9.K (GND), U$9.KK (GND), U$9.M (GND), U$9.MM (GND), U$9.P (GND), U$9.PP (GND), U$9.S (GND), U$9.SS (GND), U$9.U (GND), U$9.UU (GND), U$9.VV (GND), U$9.W (GND), U$9.Y (GND), U$10.A (GND), U$10.AA (GND), U$10.B (GND), U$10.C (GND), U$10.CC (GND), U$10.E (GND), U$10.EE (GND), U$10.H (GND), U$10.HH (GND), U$10.K (GND), U$10.KK (GND), U$10.M (GND), U$10.MM (GND), U$10.P (GND), U$10.PP (GND), U$10.S (GND), U$10.SS (GND), U$10.U (GND), U$10.UU (GND), U$10.VV (GND), U$10.W (GND), U$10.Y (GND); also elsewhere on the board
INC_MB: U$1.LL (1), U$2.LL (1), U$3.LL (1), U$4.LL (1), U$5.LL (1)
INITALIZE: U$1.RR (1), U$2.RR (1), U$3.RR (1), U$4.RR (1), U$5.RR (1)
VCC: SV2.1, SV2.20; also elsewhere on the board
WCOV: U$6.BB (1)
WCOV0: U$7.BB (1)
WCOV1: U$8.BB (1)
WCOV2: U$9.BB (1)
WCOV3: U$10.BB (1)
